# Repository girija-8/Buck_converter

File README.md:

# LMR51450 Based 7.6V, 4A DC-DC Buck Converter
---
A 2-layer PCB design for a synchronous step-down (buck) converter based on the Texas Instruments' LMR51450. This project is designed to be a power supply for general-purpose electronics, capable of operating over a wide input voltage range.

---
## Key Specifications

| Parameter | Value |
| :--- | :--- |
| **Input Voltage** | 4V to 36V DC |
| **Output Voltage** | 7.6V DC |
| **Maximum Output Current** | 4A |
| **Switching Frequency** | 500 kHz |
| **IC** | LMR51450SDRRR |

---
## Hardware

The design is revolves around the LMR51450 IC and a power inductor suitable for the required current.

* **Main Controller IC:** Texas Instruments `LMR51450SDRRR` (36V, 5A Synchronous Buck Converter)
* **Power Inductor:** Wurth Elektronik `7443845030082` (8.2µH, 6.2A I<sub>rms</sub>, 9.5A I<sub>sat</sub>)
* **Input/Output Connectors:** 2-Position, 5.08mm Pitch Screw Terminals

A complete list of all components, including specific part numbers for resistors and capacitors, is available in the Bill of Materials.

---
## Project Structure
```
Buck_Converter_Project/
│
├── Files/
│   ├── Buck_Converter.csv.xlsx
│   ├── Buck_Converter.kicad_pcb
│   ├── Buck_Converter.kicad_pro
│   ├── Buck_Converter.kicad_sch
│   └── Buck_converter_BOM.pdf
│
├── Media/
│   ├── PCB.png
│   ├── PCB_bottom.png
│   ├── PCB_top_layer.png
│   └── Schematic.png
│
└── README.md
```
---
## Key Design Equations

The primary component values were determined using the following formulas from the LMR51450 datasheet.

#### Output Voltage Resistor Divider

The output voltage ($V_{OUT}$) is set by the feedback resistors $R_{FBT}$ and $R_{FBB}$ based on the internal 0.8V reference ($V_{REF}$).

$$
R_{FBT} = \frac{(V_{OUT} - V_{REF})}{V_{REF}} \times R_{FBB}
$$

#### Inductor Selection

The minimum inductance ($L_{MIN}$) is calculated based on the maximum input voltage, desired output current, and a chosen inductor ripple current factor ($K_{IND}$, typically 0.2-0.4).

$$
L_{MIN} = \frac{V_{IN\_MAX} - V_{OUT}}{I_{OUT} \times K_{IND}} \times \frac{V_{OUT}}{V_{IN\_MAX} \times f_{SW}}
$$

#### Output Capacitor Selection

The output capacitance ($C_{OUT}$) is chosen to meet requirements for both output voltage ripple and transient response during a load step.

* **Ripple based on ESR:**

    ```math
    \Delta V_{OUT\_ESR} = \Delta i_{L} \times ESR
    ```

* **Ripple based on Capacitance:**
  
    ```math
    \Delta V_{OUT\_C} = \frac{\Delta i_{L}}{8 \times f_{SW} \times C_{OUT}}
    ```

* **Minimum Capacitance for Transient Response:**

    ```math
    C_{OUT} > \frac{1}{2} \times \frac{6 \times (I_{OH} - I_{OL})}{f_{SW} \times \Delta V_{OUT\_SHOOT}}
    ```
---
## Design Files

This repository contains all the necessary files to review and manufacture the project, designed in KiCad.

* **`Buck_Converter.kicad_sch`**: The main schematic file.
* **`Buck_Converter.kicad_pcb`**: The final 2-layer PCB layout file.
* **`Buck_Converter.csv`**: The complete Bill of Materials (BOM) with manufacturer part numbers.
* **`Buck_Converter_BOM.pdf`**: Bill of Materials (BOM) in pdf format.
* **`Media/`**: A folder containing screenshots of the final schematic and PCB layout.

---
## Design Notes & Layout Strategy

This project was designed with a focus on robustness and performance, following best practices for switching power supply layout.

* **Wide Input Range:** The components, particularly the 8.2µH inductor, were selected to ensure stable operation across the full input voltage range of the IC (up to 36V).
* **2-Layer Design:**
    * **Top Layer (`F.Cu`):** All components are placed on the top layer. High-current paths (`VIN`, `VOUT`, `SW`) are implemented as wide copper pours to minimize resistance, inductance, and thermal stress. A "filler" ground pour is also used for additional shielding.
    * **Bottom Layer (`B.Cu`):** The entire bottom layer is dedicated to a solid, continuous ground plane. This provides a low-impedance return path for currents, which is critical for stability and low noise (EMI).
* **Thermal Management:** A dense grid of thermal vias is placed directly on the central thermal pad of the LMR51450 IC, connecting it to the bottom ground plane to effectively dissipate heat. Additional "stitching" vias are used throughout the board to strongly connect the top and bottom ground planes.
* **Routing:** All high-current connections were made with copper pours. Only the low-power signal traces for the feedback network were routed as thin traces.

---
## Media

*(**Instructions:** Replace these placeholders with your final screenshots inside the `Media` folder.)*

**Schematic:**

**PCB Layout (Top and Bottom Layers):**

---

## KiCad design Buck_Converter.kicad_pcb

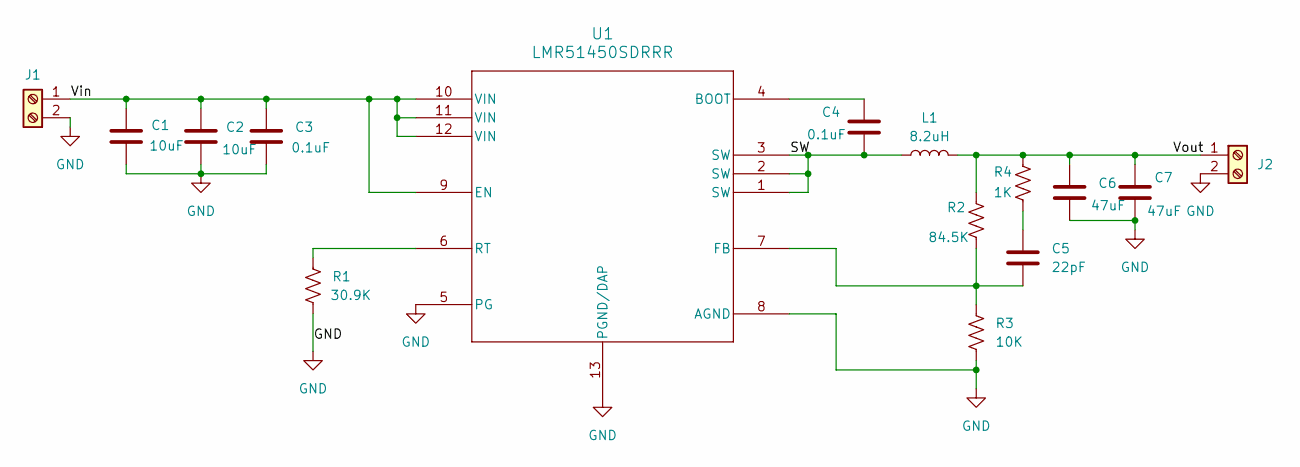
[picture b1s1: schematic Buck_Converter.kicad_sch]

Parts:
C1, C2: 10uF; C_1206_3216Metric
C3, C4: 0.1uF; C_0805_2012Metric
C5: 22pF; C_0805_2012Metric
C6, C7: 47uF; C_1210_3225Metric
J1, J2: Screw_Terminal_01x02; Samtec_HPM-02-01-x-S_Straight_1x02_Pitch5.08mm
L1: 8.2uH; L_Wurth_WE-MXGI-5030
R1: 30.9K; R_0805_2012Metric
R2: 84.5K; R_0805_2012Metric
R3: 10K; R_0805_2012Metric
R4: 1K; R_0805_2012Metric
U1: LMR51450SDRRR; WSON_SDRRR_TEX

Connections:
/SW: C4.2, L1.1, U1.1 (SW), U1.2 (SW), U1.3 (SW)
/Vin: C1.1, C2.1, C3.1, J1.1, U1.9 (EN), U1.10 (VIN), U1.11 (VIN), U1.12 (VIN)
/Vout: C6.1, C7.1, J2.1, L1.2, R2.1, R4.1
GND: C1.2, C2.2, C3.2, C6.2, C7.2, J1.2, J2.2, R1.2, R3.2, U1.5 (PG), U1.8 (AGND), U1.13 (PGND/DAP)
unnamed: C5.1, R4.2
unnamed: C4.1, U1.4 (BOOT)
unnamed: C5.2, R2.2, R3.1, U1.7 (FB)
unnamed: R1.1, U1.6 (RT)

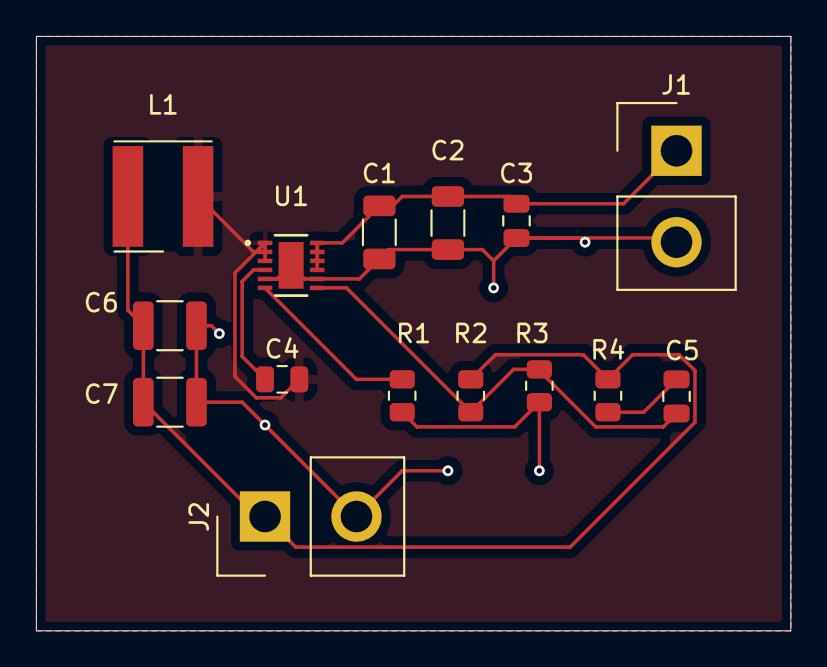
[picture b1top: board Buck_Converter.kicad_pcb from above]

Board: 2 copper layers, 41.9 x 33.0 mm, 15 parts (0 on the bottom side), 8 nets.
